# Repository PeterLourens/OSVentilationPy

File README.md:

# Functional Description Ventilation system

## Fan unit specification:
* Type: CVE ECO 2HE
* Version: 110-0031-001
* Article number: 545-5022
* Capacity: 417 m3/h
* Pressure: 150 Pa
* Nominal Power: 67.1 W
* Nominal Voltage: 230V-50Hz
* Nominal current: 0.5A
* Power factor: 0.58
* Weight: 3.5 kg

## State Machine
The ventilation system is based on a state machine library written by José Rullán in 2022. This is the state machine:

# Initial state

When the ventilation system starts, all valves should go to their default position and the fan at low (10%) speed. The default positions are:

| Valve number | Room | valve position | flow [m3/h] | High valve position [%] |
| --- | ---| --- | --- | --- |
| 0 | HR Kap | 4 | 5 | 20 |
| 1 | Keuken | 4 | 5 | 20 |
| 2 | Toliet | 4 | 5 | 20 |
| 3 | Not used | 0 | 0 | 0 |
| 4 | Not used | 0 | 0 | 0 |
| 5 | Wasruimte | 4 | 5 | 20 |
| 6 | Badkamer | 24 | 60 | |
| 7 | Not used | 0 | 0 | 0 |
| 8 | Slaapkamer1 | 4 | 5 | 20 |
| 9 | Slaapkamer 2 | 4 | 5 | 20 |
| 10 | Slaapkamer 3 | 4 | 5 | 20 |
| 11 | Slaapkamer 4 | 4 | 5 | 20 |

Fan:
* Low: 20 -> 10% = 40 m3/h
* Medium: 120 -> 50% = 200 m3/h
* High: 220 -> 100% = 400 m3/h

## Operating

| Name | Flap position | ventilation | 
| --- | --- | --- |
| Bathroom | 100 | 60-75 |

### Ventilatiepatroon/etmaal

Normal ventilation pattern:
* Laagstand 8 uur (23:00u - 07:00u) 8 uur (23:00u - 07:00u)
* Middenstand 14 uur (07:00 - 23:00)
* Hoogstand 2 uur as required, e.g. cooking or shower

### Temperature control

No temperature control. Air is drawn in through the rosters in the windows. 

### Humidity control

Humidity is measured with two sensors. Conditions:

* When bathroom1 humidity is higher than 90% then shower is on. Actions:
    * Fanspeed should be increased to high. 
    * All valves remain in the same position (bathroom1 is and remains 100% open, all other unchanged).

### CO2 Control

CO2 is measured with one sensor in the suction tube of the fan so it measures for all rooms. Conditions and actions:

* When CO2 is high (1000ppm) in daytime the ventilation should be increased. Actions:
    * Valves remain in same position 
    * fanspeed should be increased to high until CO2 level has decreased to 800 ppm.
* When CO2 is high during night time, the bedrooms should be ventilated more. Actions 
    * Open the valves to 100% of all bedrooms (but not in the office). 
    * Fanspeed remains on low

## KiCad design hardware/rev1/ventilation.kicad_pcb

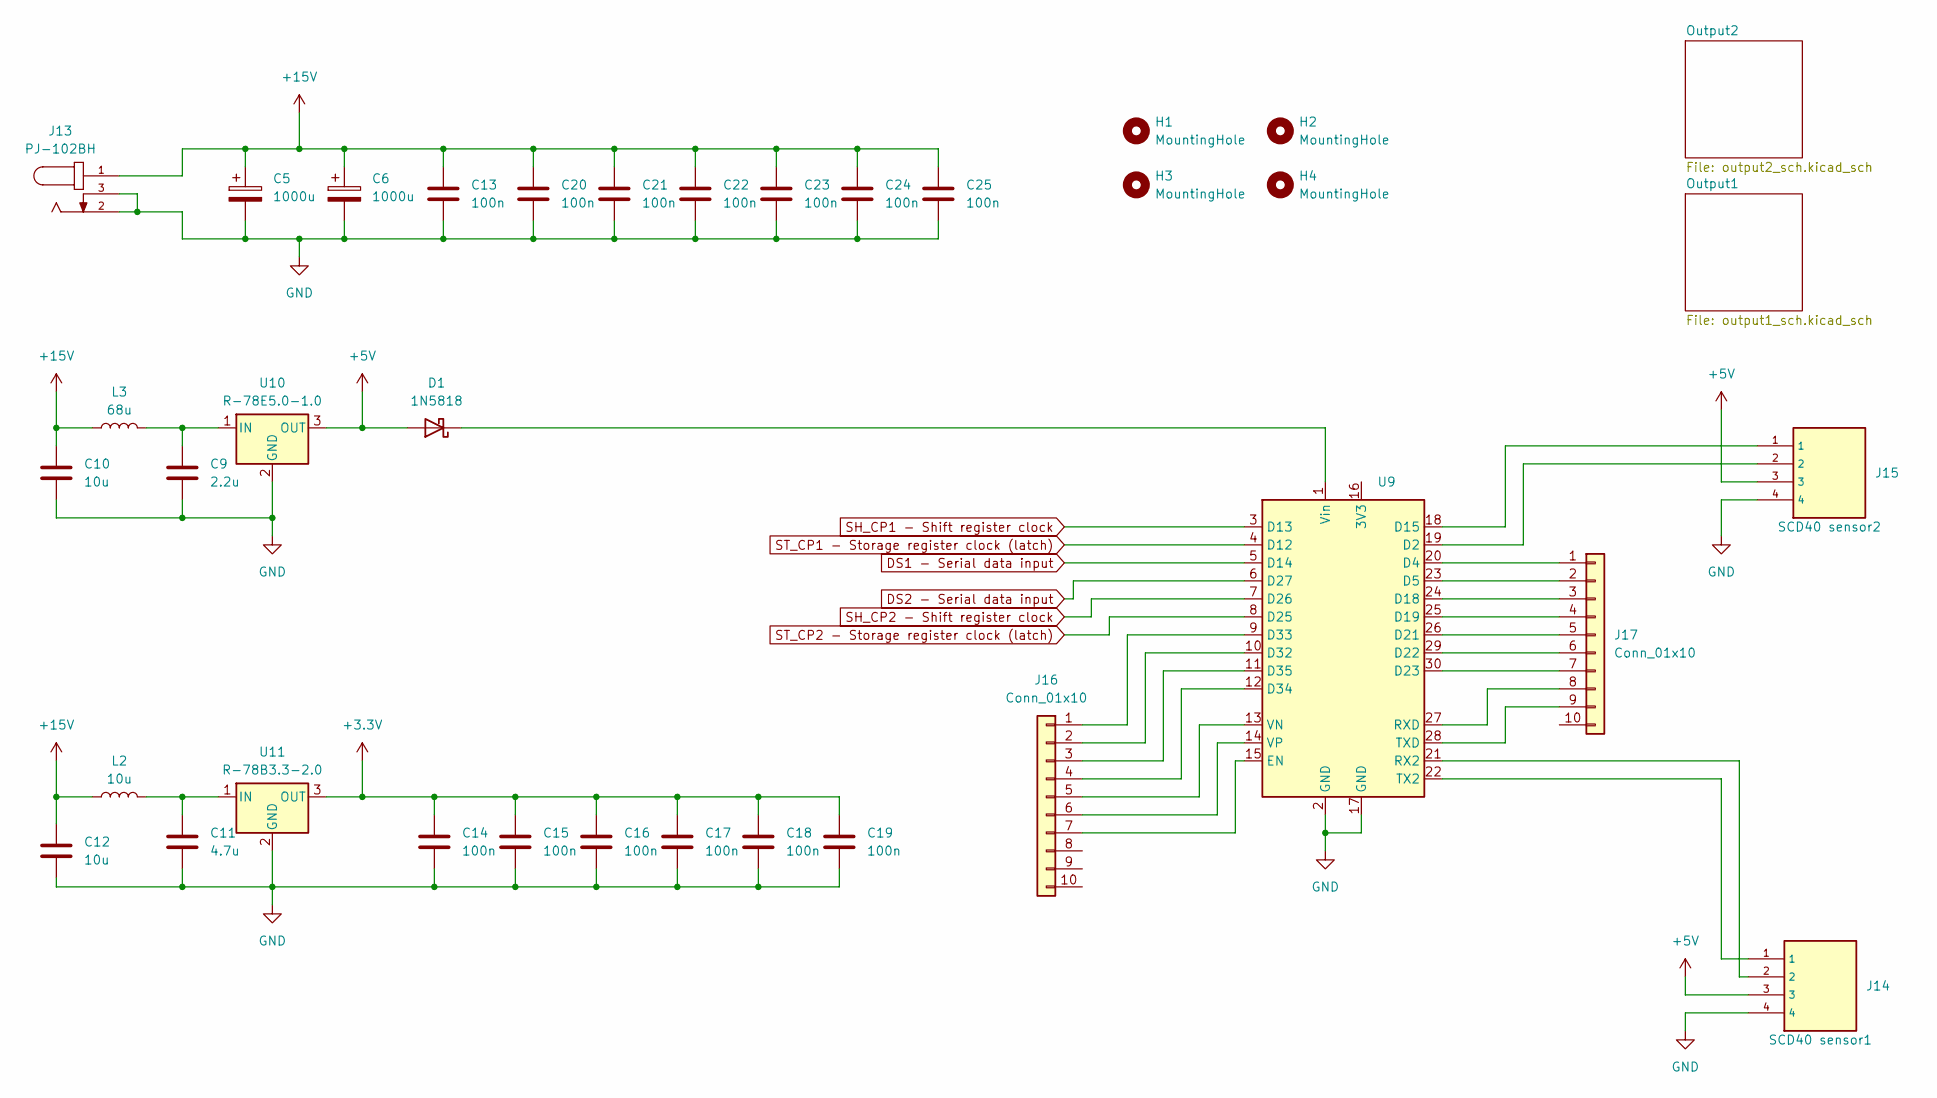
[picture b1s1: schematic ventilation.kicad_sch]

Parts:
C5, C6: 1000u; CP_Radial_D12.5mm_P5.00mm
C9: 2.2u; C_Axial_L5.1mm_D3.1mm_P7.50mm_Horizontal
C10, C12: 10u; C_Axial_L5.1mm_D3.1mm_P7.50mm_Horizontal
C11: 4.7u; C_Axial_L5.1mm_D3.1mm_P7.50mm_Horizontal
C13, C20, C21, C22, C23, C24, C25: 100n; C_Axial_L3.8mm_D2.6mm_P7.50mm_Horizontal
C14, C15, C16, C17, C18, C19: 100n; C_Disc_D3.8mm_W2.6mm_P2.50mm
D1: 1N5818; D_DO-41_SOD81_P10.16mm_Horizontal
H1, H2, H3, H4: MountingHole; MountingHole_3.2mm_M3
J13: PJ-102BH; CUI_PJ-102BH; PART_REV 1.02
J14: SCD40 sensor1; SEEED_110990030
J15: SCD40 sensor2; SEEED_110990030
J16, J17: Conn_01x10; PinHeader_1x10_P2.54mm_Vertical
L2: 10u; L_Radial_D8.7mm_P5.00mm_Fastron_07HCP
L3: 68u; L_Radial_D8.7mm_P5.00mm_Fastron_07HCP
U9: NodeMCU-32S 30 pins Ali
U10: R-78E5.0-1.0; Converter_DCDC_RECOM_R-78E-0.5_THT
U11: R-78B3.3-2.0; Converter_DCDC_RECOM_R-78B-2.0_THT

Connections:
+3.3V: C14.1, C15.1, C16.1, C17.1, C18.1, C19.1, U11.3 (OUT); also elsewhere on the board
+5V: D1.2 (A), J14.3, J15.3, U10.3 (OUT)
+15V: C5.1, C6.1, C10.1, C12.1, C13.1, C20.1, C21.1, C22.1, C23.1, C24.1, C25.1, J13.1, L2.1, L3.1; also elsewhere on the board
DS1 - Serial data input: U9.5 (D14); also elsewhere on the board
DS2 - Serial data input: U9.6 (D27); also elsewhere on the board
GND: C5.2, C6.2, C9.2, C10.2, C11.2, C12.2, C13.2, C14.2, C15.2, C16.2, C17.2, C18.2, C19.2, C20.2, C21.2, C22.2, C23.2, C24.2, C25.2, J13.2, J13.3, J14.4, J15.4, U9.2 (GND), U9.17 (GND), U10.2 (GND), U11.2 (GND); also elsewhere on the board
unnamed: D1.1 (K), U9.1 (Vin)
unnamed: J16.1, U9.9 (D33)
unnamed: J16.2, U9.10 (D32)
unnamed: J16.3, U9.11 (D35)
unnamed: J16.4, U9.12 (D34)
unnamed: J16.5, U9.13 (VN)
unnamed: J16.6, U9.14 (VP)
unnamed: J16.7, U9.15 (EN)
unnamed: J17.1, U9.20 (D4)
unnamed: J17.2, U9.23 (D5)
unnamed: J17.3, U9.24 (D18)
unnamed: J17.4, U9.25 (D19)
unnamed: J17.5, U9.26 (D21)
unnamed: J17.6, U9.29 (D22)
unnamed: J17.7, U9.30 (D23)
unnamed: J17.8, U9.27 (RXD)
unnamed: J17.9, U9.28 (TXD)
unnamed: J15.2, U9.19 (D2)
unnamed: J15.1, U9.18 (D15)
unnamed: J14.2, U9.21 (RX2)
unnamed: J14.1, U9.22 (TX2)
unnamed: C9.1, L3.2, U10.1 (IN)
unnamed: C11.1, L2.2, U11.1 (IN)
SH_CP1 - Shift register clock: U9.3 (D13); also elsewhere on the board
SH_CP2 - Shift register clock: U9.7 (D26); also elsewhere on the board
ST_CP1 - Storage register clock (latch): U9.4 (D12); also elsewhere on the board
ST_CP2 - Storage register clock (latch): U9.8 (D25); also elsewhere on the board

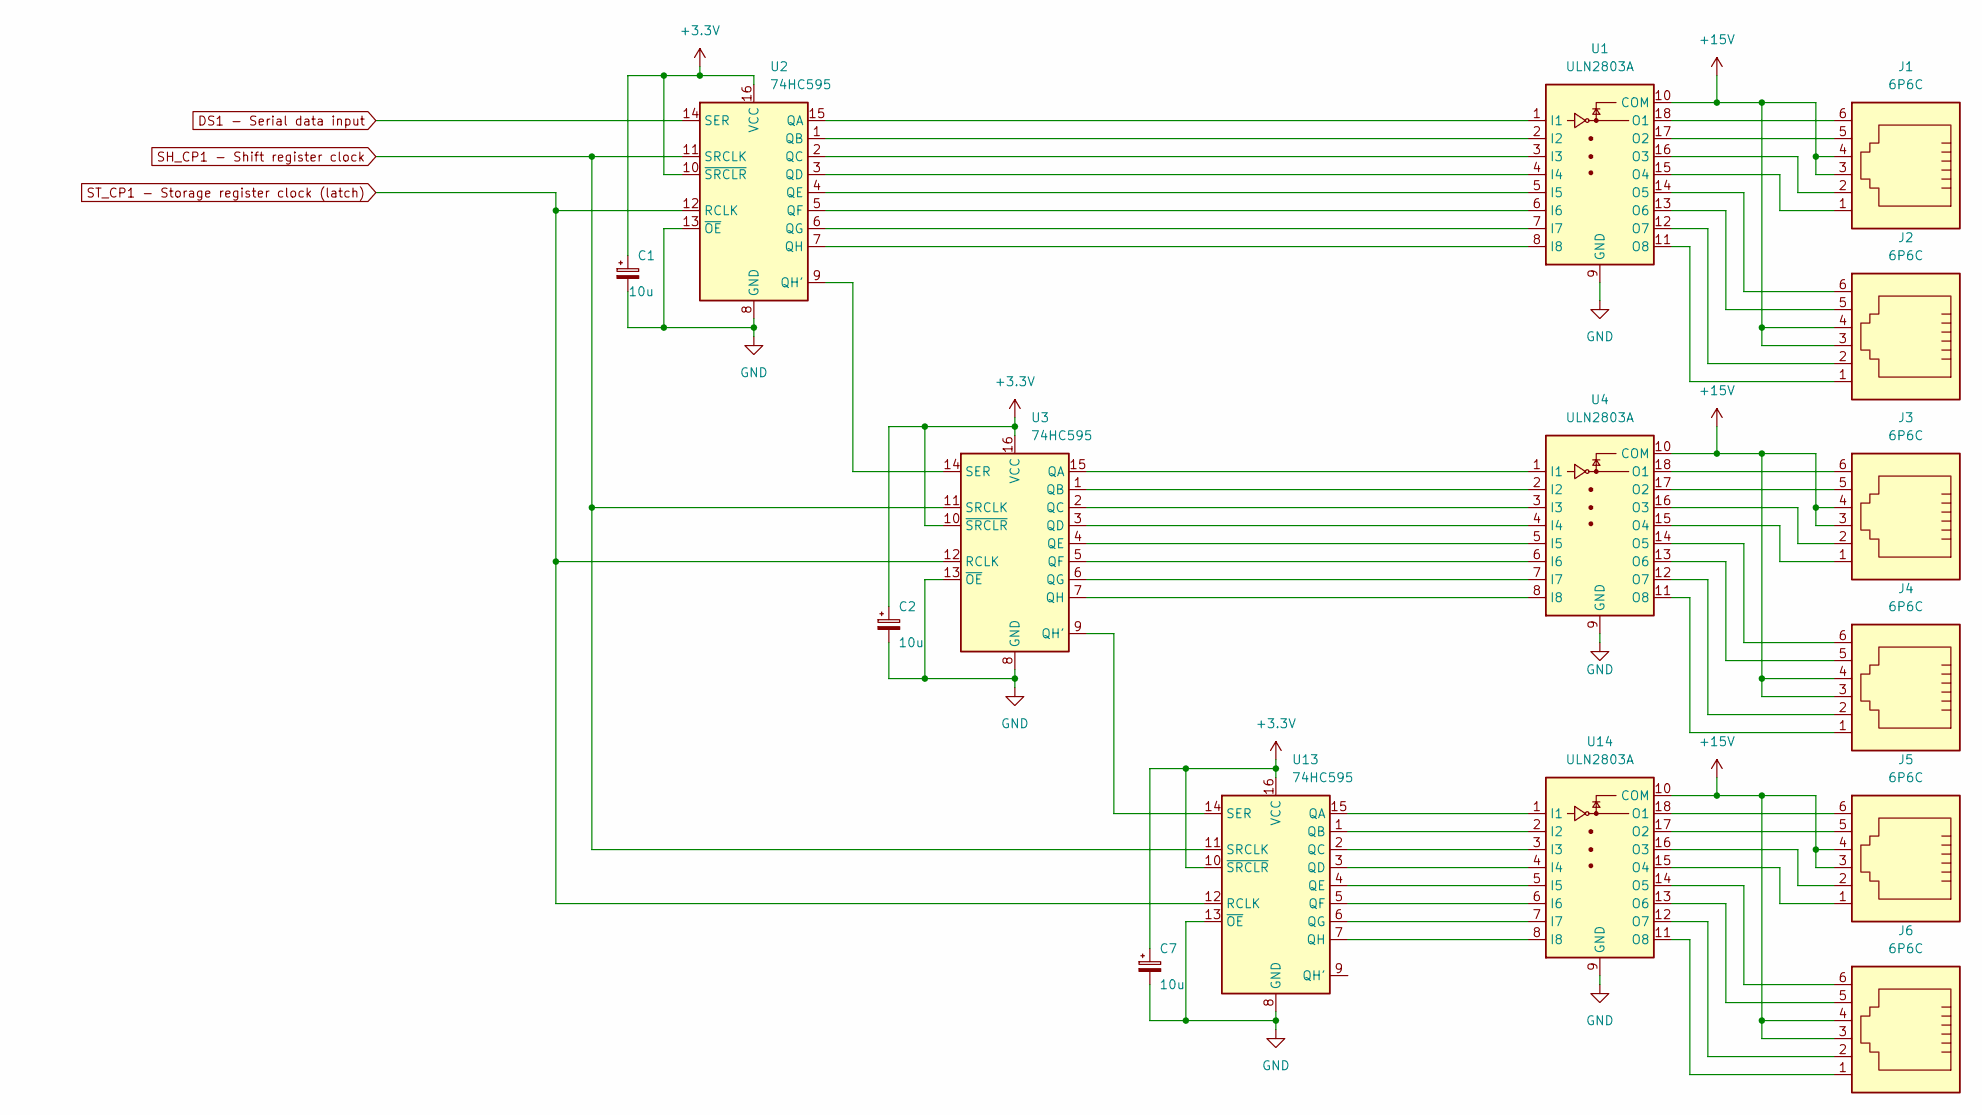
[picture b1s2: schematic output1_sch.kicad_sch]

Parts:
C1, C2, C7: 10u; CP_Radial_D5.0mm_P2.00mm
J1, J2, J3, J4, J5, J6: 6P6C; 615006138421
U1, U4, U14: ULN2803A; DIP-18_W7.62mm_Socket
U2, U3, U13: 74HC595; DIP-16_W7.62mm_Socket

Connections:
+3.3V: C1.1, C2.1, C7.1, U2.10 (~SRCLR), U2.16 (VCC), U3.10 (~SRCLR), U3.16 (VCC), U13.10 (~SRCLR), U13.16 (VCC); also elsewhere on the board
+15V: J1.3, J1.4, J2.3, J2.4, J3.3, J3.4, J4.3, J4.4, J5.3, J5.4, J6.3, J6.4, U1.10 (COM), U4.10 (COM), U14.10 (COM); also elsewhere on the board
DS1 - Serial data input: U2.14 (SER); also elsewhere on the board
GND: C1.2, C2.2, C7.2, U1.9 (GND), U2.8 (GND), U2.13 (~OE), U3.8 (GND), U3.13 (~OE), U4.9 (GND), U13.8 (GND), U13.13 (~OE), U14.9 (GND); also elsewhere on the board
unnamed: U1.1 (I1), U2.15 (QA)
unnamed: U1.2 (I2), U2.1 (QB)
unnamed: U1.3 (I3), U2.2 (QC)
unnamed: U1.4 (I4), U2.3 (QD)
unnamed: U1.5 (I5), U2.4 (QE)
unnamed: U1.6 (I6), U2.5 (QF)
unnamed: U1.7 (I7), U2.6 (QG)
unnamed: U1.8 (I8), U2.7 (QH)
unnamed: J1.6, U1.18 (O1)
unnamed: J1.5, U1.17 (O2)
unnamed: J1.2, U1.16 (O3)
unnamed: J1.1, U1.15 (O4)
unnamed: J2.6, U1.14 (O5)
unnamed: J2.5, U1.13 (O6)
unnamed: J2.2, U1.12 (O7)
unnamed: J2.1, U1.11 (O8)
unnamed: U2.9 (QH'), U3.14 (SER)
unnamed: U3.15 (QA), U4.1 (I1)
unnamed: U3.1 (QB), U4.2 (I2)
unnamed: U3.2 (QC), U4.3 (I3)
unnamed: U3.3 (QD), U4.4 (I4)
unnamed: U3.4 (QE), U4.5 (I5)
unnamed: U3.5 (QF), U4.6 (I6)
unnamed: U3.6 (QG), U4.7 (I7)
unnamed: U3.7 (QH), U4.8 (I8)
unnamed: J3.6, U4.18 (O1)
unnamed: J3.5, U4.17 (O2)
unnamed: J3.2, U4.16 (O3)
unnamed: J3.1, U4.15 (O4)
unnamed: J4.6, U4.14 (O5)
unnamed: J4.5, U4.13 (O6)
unnamed: J4.2, U4.12 (O7)
unnamed: J4.1, U4.11 (O8)
unnamed: U13.15 (QA), U14.1 (I1)
unnamed: U13.1 (QB), U14.2 (I2)
unnamed: U13.2 (QC), U14.3 (I3)
unnamed: U13.3 (QD), U14.4 (I4)
unnamed: U13.4 (QE), U14.5 (I5)
unnamed: U13.5 (QF), U14.6 (I6)
unnamed: U13.6 (QG), U14.7 (I7)
unnamed: U13.7 (QH), U14.8 (I8)
unnamed: U3.9 (QH'), U13.14 (SER)
unnamed: J5.6, U14.18 (O1)
unnamed: J5.5, U14.17 (O2)
unnamed: J5.2, U14.16 (O3)
unnamed: J5.1, U14.15 (O4)
unnamed: J6.6, U14.14 (O5)
unnamed: J6.5, U14.13 (O6)
unnamed: J6.2, U14.12 (O7)
unnamed: J6.1, U14.11 (O8)
SH_CP1 - Shift register clock: U2.11 (SRCLK), U3.11 (SRCLK), U13.11 (SRCLK); also elsewhere on the board
ST_CP1 - Storage register clock (latch): U2.12 (RCLK), U3.12 (RCLK), U13.12 (RCLK); also elsewhere on the board

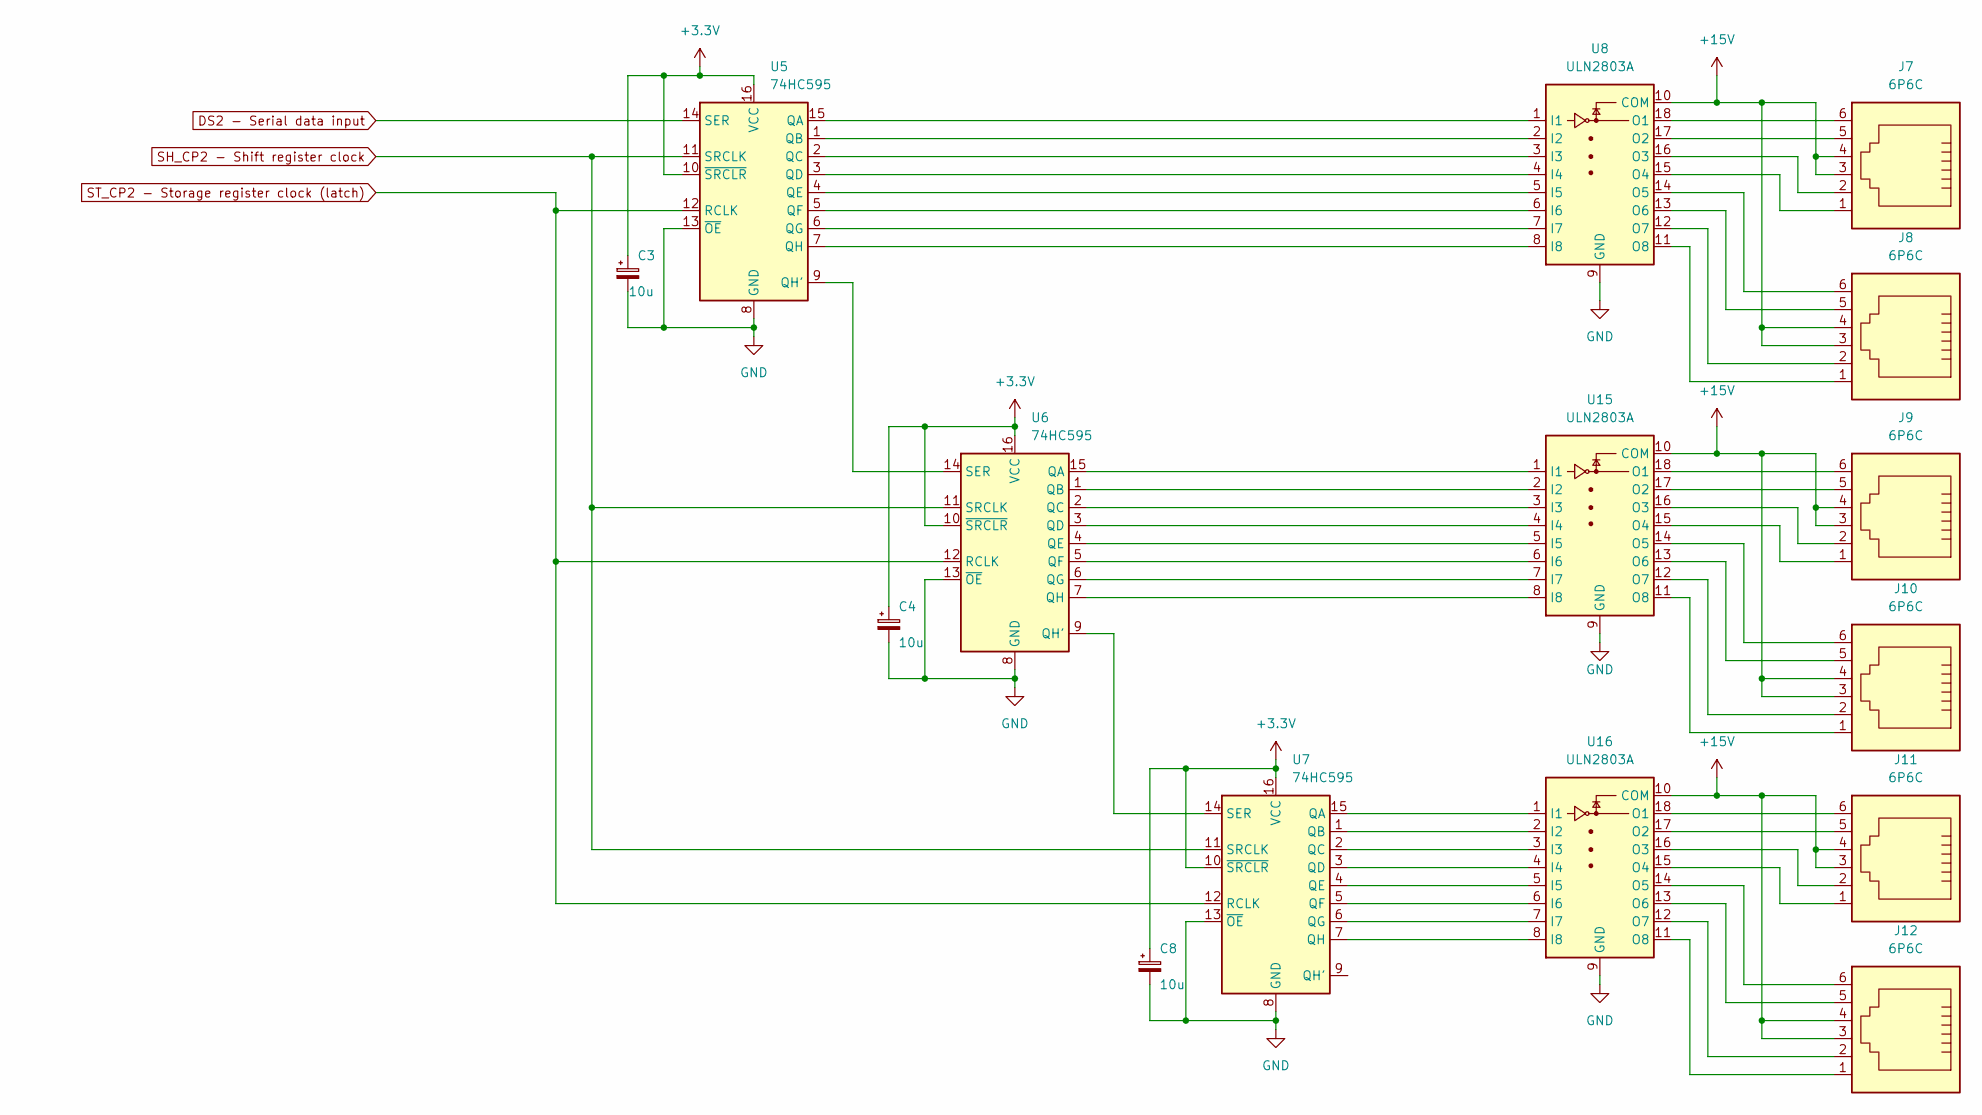
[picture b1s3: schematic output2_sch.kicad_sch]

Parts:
C3, C4, C8: 10u; CP_Radial_D5.0mm_P2.00mm
J7, J8, J9, J10, J11, J12: 6P6C; 615006138421
U5, U6, U7: 74HC595; DIP-16_W7.62mm_Socket
U8, U15, U16: ULN2803A; DIP-18_W7.62mm_Socket

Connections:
+3.3V: C3.1, C4.1, C8.1, U5.10 (~SRCLR), U5.16 (VCC), U6.10 (~SRCLR), U6.16 (VCC), U7.10 (~SRCLR), U7.16 (VCC); also elsewhere on the board
+15V: J7.3, J7.4, J8.3, J8.4, J9.3, J9.4, J10.3, J10.4, J11.3, J11.4, J12.3, J12.4, U8.10 (COM), U15.10 (COM), U16.10 (COM); also elsewhere on the board
DS2 - Serial data input: U5.14 (SER); also elsewhere on the board
GND: C3.2, C4.2, C8.2, U5.8 (GND), U5.13 (~OE), U6.8 (GND), U6.13 (~OE), U7.8 (GND), U7.13 (~OE), U8.9 (GND), U15.9 (GND), U16.9 (GND); also elsewhere on the board
unnamed: U5.15 (QA), U8.1 (I1)
unnamed: U5.1 (QB), U8.2 (I2)
unnamed: U5.2 (QC), U8.3 (I3)
unnamed: U5.3 (QD), U8.4 (I4)
unnamed: U5.4 (QE), U8.5 (I5)
unnamed: U5.5 (QF), U8.6 (I6)
unnamed: U5.6 (QG), U8.7 (I7)
unnamed: U5.9 (QH'), U6.14 (SER)
unnamed: U5.7 (QH), U8.8 (I8)
unnamed: U6.9 (QH'), U7.14 (SER)
unnamed: J7.6, U8.18 (O1)
unnamed: J7.5, U8.17 (O2)
unnamed: J7.2, U8.16 (O3)
unnamed: J7.1, U8.15 (O4)
unnamed: J8.6, U8.14 (O5)
unnamed: J8.5, U8.13 (O6)
unnamed: J8.2, U8.12 (O7)
unnamed: J8.1, U8.11 (O8)
unnamed: U6.15 (QA), U15.1 (I1)
unnamed: U6.1 (QB), U15.2 (I2)
unnamed: U6.2 (QC), U15.3 (I3)
unnamed: U6.3 (QD), U15.4 (I4)
unnamed: U6.4 (QE), U15.5 (I5)
unnamed: U6.5 (QF), U15.6 (I6)
unnamed: U6.6 (QG), U15.7 (I7)
unnamed: U6.7 (QH), U15.8 (I8)
unnamed: J9.6, U15.18 (O1)
unnamed: J9.5, U15.17 (O2)
unnamed: J9.2, U15.16 (O3)
unnamed: J9.1, U15.15 (O4)
unnamed: J10.6, U15.14 (O5)
unnamed: J10.5, U15.13 (O6)
unnamed: J10.2, U15.12 (O7)
unnamed: J10.1, U15.11 (O8)
unnamed: U7.15 (QA), U16.1 (I1)
unnamed: U7.1 (QB), U16.2 (I2)
unnamed: U7.2 (QC), U16.3 (I3)
unnamed: U7.3 (QD), U16.4 (I4)
unnamed: U7.4 (QE), U16.5 (I5)
unnamed: U7.5 (QF), U16.6 (I6)
unnamed: U7.6 (QG), U16.7 (I7)
unnamed: U7.7 (QH), U16.8 (I8)
unnamed: J11.6, U16.18 (O1)
unnamed: J11.5, U16.17 (O2)
unnamed: J11.2, U16.16 (O3)
unnamed: J11.1, U16.15 (O4)
unnamed: J12.6, U16.14 (O5)
unnamed: J12.5, U16.13 (O6)
unnamed: J12.2, U16.12 (O7)
unnamed: J12.1, U16.11 (O8)
SH_CP2 - Shift register clock: U5.11 (SRCLK), U6.11 (SRCLK), U7.11 (SRCLK); also elsewhere on the board
ST_CP2 - Storage register clock (latch): U5.12 (RCLK), U6.12 (RCLK), U7.12 (RCLK); also elsewhere on the board

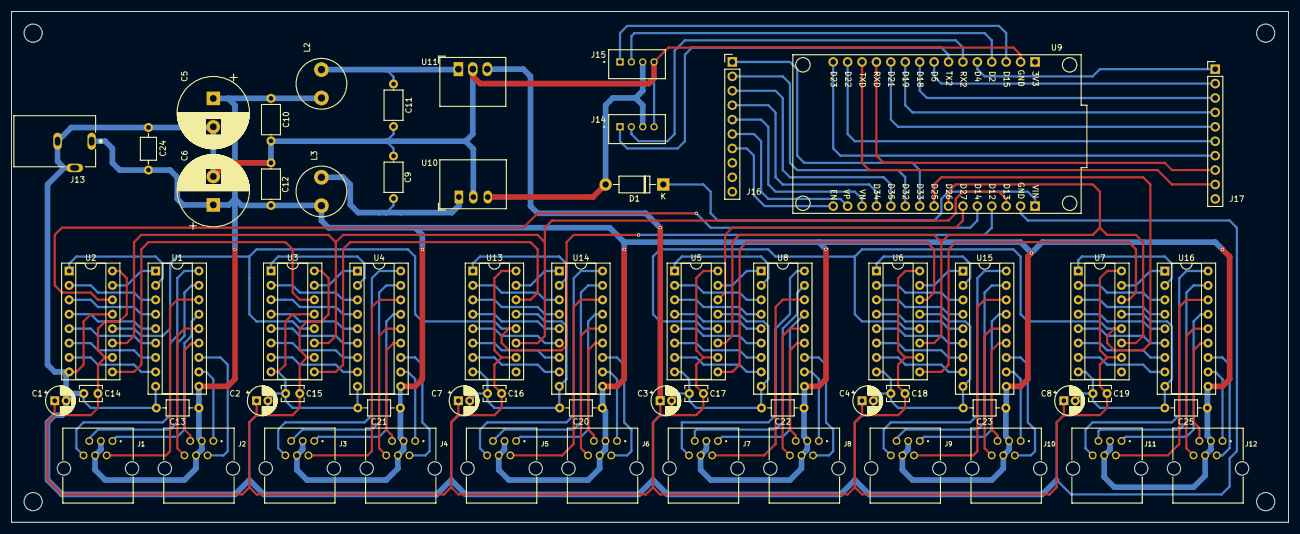
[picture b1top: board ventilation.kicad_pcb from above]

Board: 2 copper layers, 225.0 x 90.0 mm, 64 parts (0 on the bottom side), 133 nets.

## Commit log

2024-10-11 Add scratchbook.py
2024-10-12 add 2 CO2 states to main.py
2024-10-13 start with subscribe to remote topic in main.py
2024-10-15 update main.py to include manual high speed mode
2024-10-16 updated statemachine drawing and state transistion matrix
2024-10-18 Add simple.py
2024-10-18 Add robust.py
2024-10-26 Add secrets.py
2024-10-27 deleted unnesscary files
2024-10-27 ignored some files and added secets.py.example
2024-10-27 Added hardware design
2024-10-27 Added README.md
2024-10-27 Deleted pymakr.conf file
2024-10-29 Add connect.py
2024-10-30 Updated json file
2024-11-03 Change stateTransitionMatrix.json file to delete unused states
2024-11-03 Adjusted gitignaore
2024-11-07 Add main2.py
2024-12-09 Add itho_parameters.md
